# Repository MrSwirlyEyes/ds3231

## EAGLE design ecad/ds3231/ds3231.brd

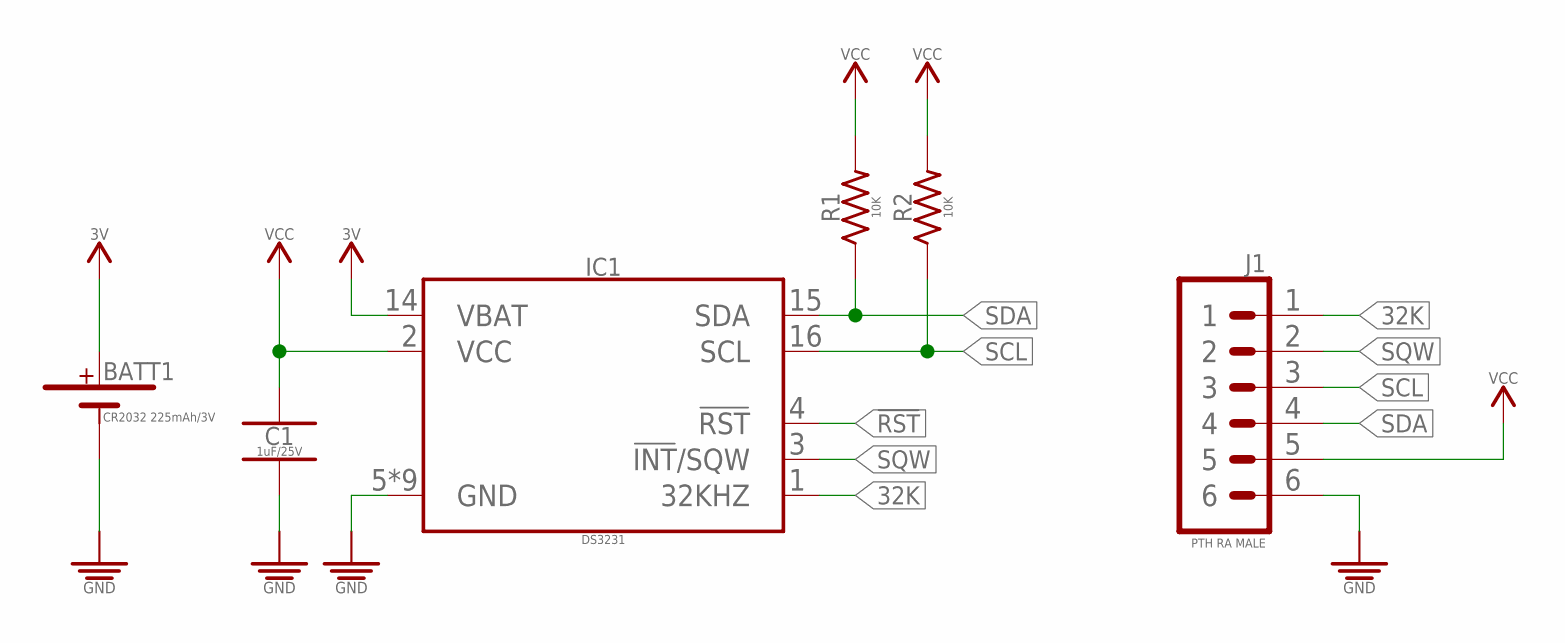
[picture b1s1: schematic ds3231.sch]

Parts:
BATT1: CR2032 225mAh/3V; CR-2032
C1: 1uF/25V; CAPC1005X55_SMD-0402
IC1: DS3231; SOIC127P1032X265-16
J1: PTH RA MALE; HDRRA6W64P254_1X6_1524X254X254B
R1, R2: 10K; RESC1005X35_SMD-0402

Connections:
3V: BATT1.+_1 (+), BATT1.+_2 (+), IC1.14 (VBAT)
32K: IC1.1 (32KHZ), J1.1
!RST: IC1.4 (!RST)
GND: BATT1.-, C1.2, IC1.5 (GND), IC1.6 (GND), IC1.7 (GND), IC1.8 (GND), IC1.9 (GND), IC1.10 (GND), IC1.11 (GND), IC1.12 (GND), IC1.13 (GND), J1.6
SCL: IC1.16 (SCL), J1.3, R2.1
SDA: IC1.15 (SDA), J1.4, R1.1
SQW: IC1.3 (!INT!/SQW), J1.2
VCC: C1.1, IC1.2 (VCC), J1.5, R1.2, R2.2

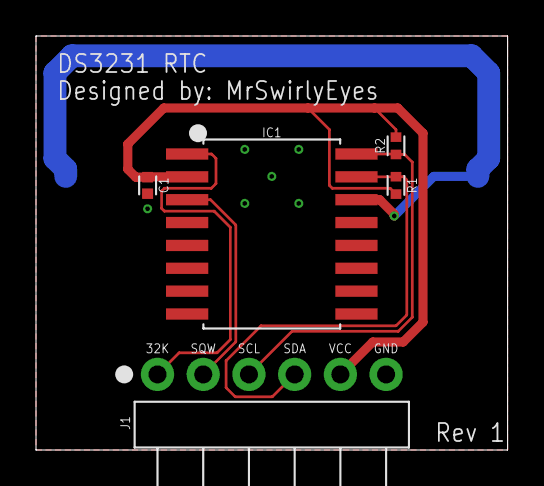
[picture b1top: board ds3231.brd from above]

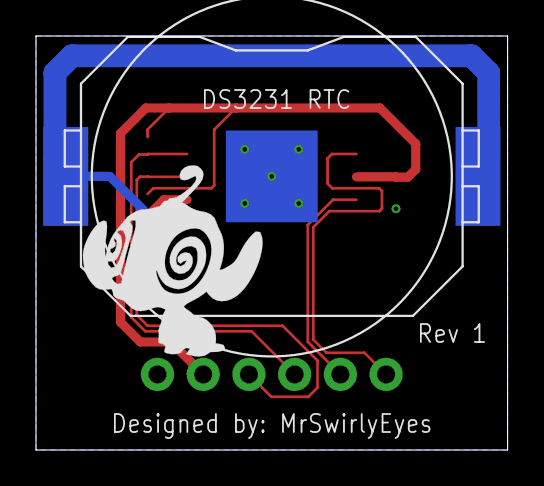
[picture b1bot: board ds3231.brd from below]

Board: 2 copper layers, 26.2 x 23.0 mm, 7 parts (2 on the bottom side), 7 nets.

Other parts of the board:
U$1: MRSWIRLYEYES-LOGO

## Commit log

2018-12-01 Initialize DS3231 repo.
2018-12-30 Add DS3231 library and ecad files.
2018-12-30 Changed 5V to 3.3V in arduino to ds3231.
2018-12-31 Update name of example scripts.
2019-01-01 Commented some of the code.
2019-02-04 Fixed discrepencies in DS3231 RTC library and example code.
2019-02-08 Updated DS3231 board to show the pin labels. Updated Set Time Auto code to properly parse the date and time if the day of the month is less than 10.
2019-02-26 Create DS3231 breakout vesion. Updated libraries.
2022-06-12 Update file format and naming. Update folder structure.
